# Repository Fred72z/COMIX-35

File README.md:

# COMIX-35 revision 1.2a

Le COMIX-35 est la réplique d'un ordinateur des années 1980, le COMX-35.
Il utilise le processeur COSMAC 1802 et dispose de 32K de mémoire vive et 3K de mémoir vidéo.

Cette version (1.2a) est une légère amélioration du COMIX-35 réalisé par "schlae".  
https://github.com/schlae/comix-35

Les améliorations sont : 
- le pcb est moins large (295mm) pour faciliter l'impression d'un boîtier
- les résistances ajustables sont verticales et plus petites
- le potentiomètre de volume est sur le côté G
- l'inter d'alimentation est vertical
- le connecteur d'extension est un modèle IDC 40 broches
- le circuit K7in est remplacé par un LM358 pour faciliter le chargement sans réglage de seuil.

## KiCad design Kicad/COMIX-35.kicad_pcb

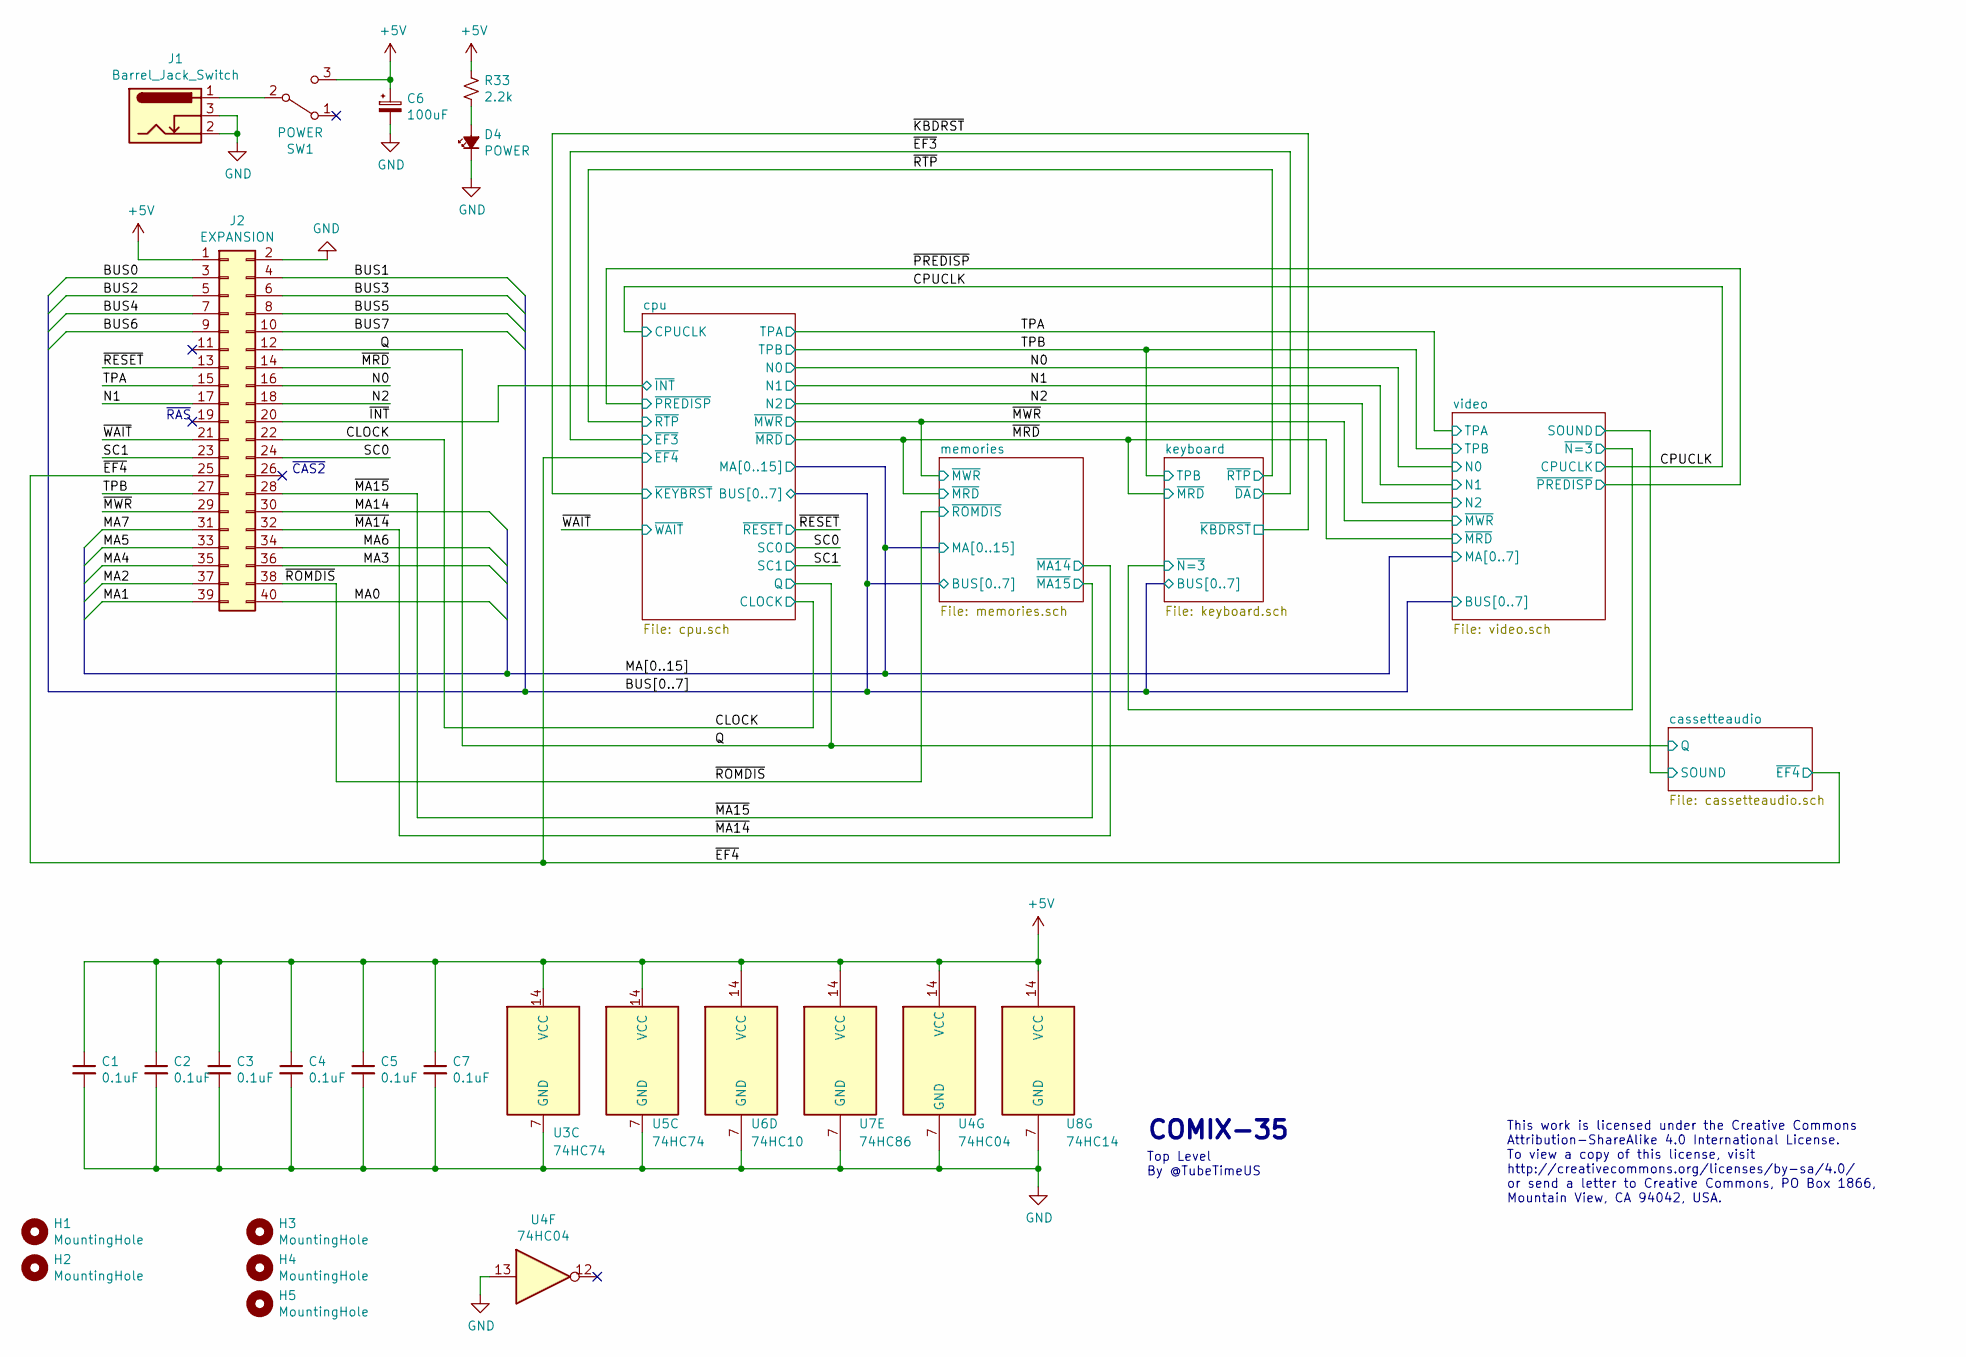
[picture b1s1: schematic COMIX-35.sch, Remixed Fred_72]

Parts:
C1, C2, C3, C4, C5, C7: 0.1uF; CAPAC200; Mouser 581-SA105E104M
C6: 100uF; CAPAE200P500X1100; Mouser 667-ECA-1CM101I
D4: POWER; LED_D5.0mm; Mouser 859-LTL-4213
H1, H2, H3, H4, H5: MountingHole; MountingHole_3.2mm_M3_DIN965
J1: Barrel_Jack_Switch; CUI_PJ-002B; Mouser 490-PJ-002B
J2: EXPANSION; IDC-Header_2x20_P2.54mm_Horizontal
R33: 2.2k; RESA500; Mouser 603-CFR-25JR-52220R
SW1: POWER; T8020L; Mouser 633-CS12ANW03
U3, U5: 74HC74; DIP-14_W7.62mm; Mouser 595-SN74HC74N
U4: 74HC04; DIP-14_W7.62mm; Mouser 595-SN74HCU04N
U6: 74HC10; DIP-14_W7.62mm; Mouser 595-SN74HC10N
U7: 74HC86; DIP-14_W7.62mm; Mouser 595-SN74HC86N
U8: 74HC14; DIP-14_W7.62mm; Mouser 595-SN74HC14N

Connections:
+5V: C1.1, C2.1, C3.1, C4.1, C5.1, C6.1, C7.1, J2.1, R33.2, SW1.3 (C), U3.14 (VCC), U4.14 (VCC), U5.14 (VCC), U6.14 (VCC), U7.14 (VCC), U8.14 (VCC); also elsewhere on the board
/BUS0: J2.3; also elsewhere on the board
/BUS1: J2.4; also elsewhere on the board
/BUS2: J2.5; also elsewhere on the board
/BUS3: J2.6; also elsewhere on the board
/BUS4: J2.7; also elsewhere on the board
/BUS5: J2.8; also elsewhere on the board
/BUS6: J2.9; also elsewhere on the board
/BUS7: J2.10; also elsewhere on the board
/CLOCK: J2.22; also elsewhere on the board
/MA0: J2.40; also elsewhere on the board
/MA1: J2.39; also elsewhere on the board
/MA2: J2.37; also elsewhere on the board
/MA3: J2.36; also elsewhere on the board
/MA4: J2.35; also elsewhere on the board
/MA5: J2.33; also elsewhere on the board
/MA6: J2.34; also elsewhere on the board
/MA7: J2.31; also elsewhere on the board
/MA14: J2.30; also elsewhere on the board
/N0: J2.16; also elsewhere on the board
/N1: J2.17; also elsewhere on the board
/N2: J2.18; also elsewhere on the board
/Q: J2.12; also elsewhere on the board
/SC0: J2.24; also elsewhere on the board
/SC1: J2.23; also elsewhere on the board
/TPA: J2.15; also elsewhere on the board
/TPB: J2.27; also elsewhere on the board
/~EF4: J2.25; also elsewhere on the board
/~INT: J2.20; also elsewhere on the board
/~MA14: J2.32; also elsewhere on the board
/~MA15: J2.28; also elsewhere on the board
/~MRD: J2.14; also elsewhere on the board
/~MWR: J2.29; also elsewhere on the board
/~RESET: J2.13; also elsewhere on the board
/~ROMDIS: J2.38; also elsewhere on the board
/~WAIT: J2.21; also elsewhere on the board
GND: C1.2, C2.2, C3.2, C4.2, C5.2, C6.2, C7.2, D4.1 (K), J1.2, J1.3, J2.2, U3.7 (GND), U4.7 (GND), U4.13, U5.7 (GND), U6.7 (GND), U7.7 (GND), U8.7 (GND); also elsewhere on the board
unnamed: D4.2 (A), R33.1
unnamed: J1.1, SW1.2 (B)

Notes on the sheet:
~RAS
~CAS2
This work is licensed under the Creative Commons Attribution-ShareAlike 4.0 International License. To view a copy of this license, visit http://creativecommons.org/licenses/by-sa/4.0/ or send a letter to Creative Commons, PO Box 1866, Mountain View, CA 94042, USA.
COMIX-35
Top Level By @TubeTimeUS

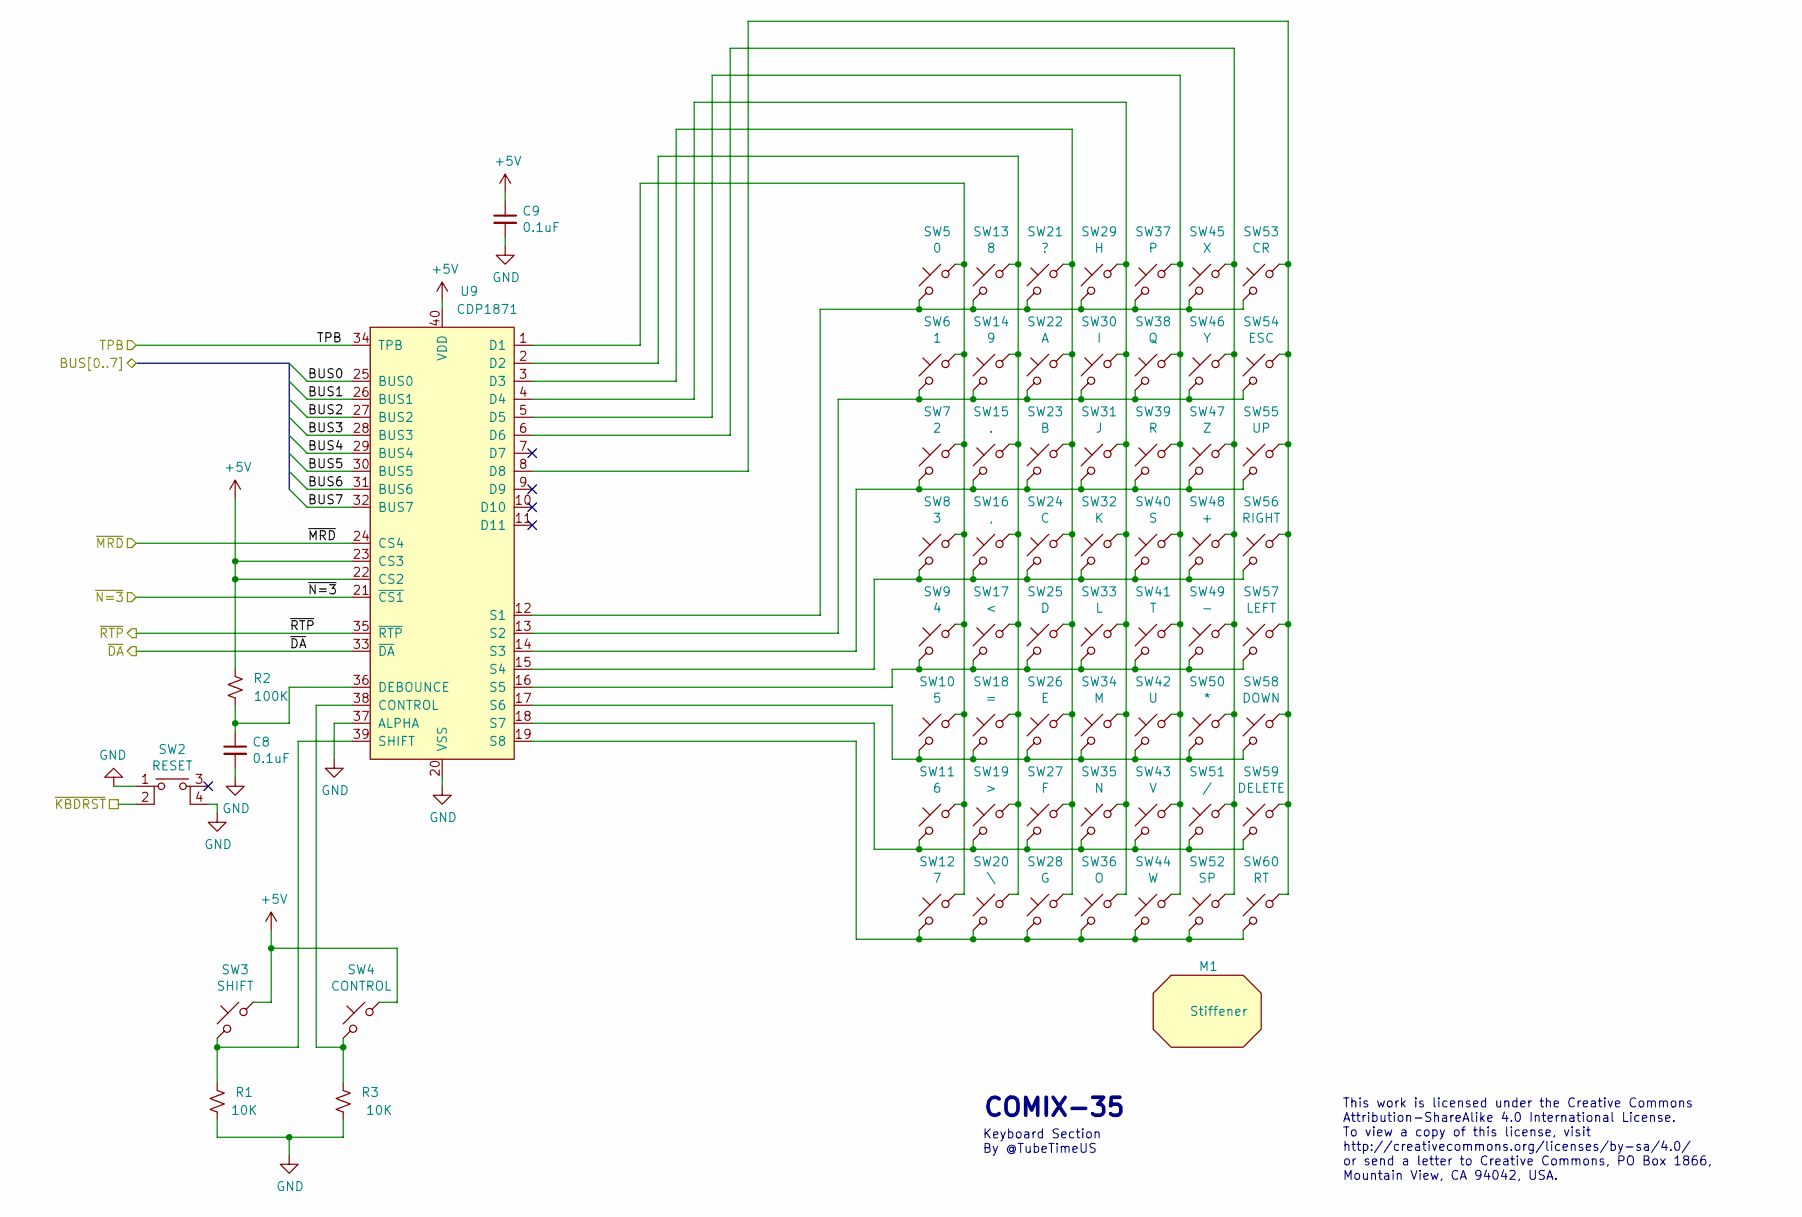
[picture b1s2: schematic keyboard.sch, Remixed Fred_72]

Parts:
C8, C9: 0.1uF; CAPAC200; Mouser 581-SA105E104M
M1: Stiffener; CHERRY_ST2; Mouser 540-0G990743
R1, R3: 10K; RESA500; Mouser 603-CFR-25JB-52-10K
R2: 100K; RESA500; Mouser 603-CFR-25JB-52-100K
SW2: RESET; SW_Tactile_SPST_Angled_PTS645Vx58-2LFS; Mouser 612-TL1105B
SW3: SHIFT; CHERRY_MX_125; Mouser 540-MX1A-11NW
SW4: CONTROL; CHERRY_MX; Mouser 540-MX1A-11NW
SW5: 0; CHERRY_MX; Mouser 540-MX1A-11NW
SW6: 1; CHERRY_MX; Mouser 540-MX1A-11NW
SW7: 2; CHERRY_MX; Mouser 540-MX1A-11NW
SW8: 3; CHERRY_MX; Mouser 540-MX1A-11NW
SW9: 4; CHERRY_MX; Mouser 540-MX1A-11NW
SW10: 5; CHERRY_MX; Mouser 540-MX1A-11NW
SW11: 6; CHERRY_MX; Mouser 540-MX1A-11NW
SW12: 7; CHERRY_MX; Mouser 540-MX1A-11NW
SW13: 8; CHERRY_MX; Mouser 540-MX1A-11NW
SW14: 9; CHERRY_MX; Mouser 540-MX1A-11NW
SW15: .; CHERRY_MX; Mouser 540-MX1A-11NW
SW16: ,; CHERRY_MX; Mouser 540-MX1A-11NW
SW17: <; CHERRY_MX; Mouser 540-MX1A-11NW
SW18: =; CHERRY_MX; Mouser 540-MX1A-11NW
SW19: >; CHERRY_MX; Mouser 540-MX1A-11NW
SW20: \\; CHERRY_MX; Mouser 540-MX1A-11NW
SW21: ?; CHERRY_MX; Mouser 540-MX1A-11NW
SW22: A; CHERRY_MX; Mouser 540-MX1A-11NW
SW23: B; CHERRY_MX; Mouser 540-MX1A-11NW
SW24: C; CHERRY_MX; Mouser 540-MX1A-11NW
SW25: D; CHERRY_MX; Mouser 540-MX1A-11NW
SW26: E; CHERRY_MX; Mouser 540-MX1A-11NW
SW27: F; CHERRY_MX; Mouser 540-MX1A-11NW
SW28: G; CHERRY_MX; Mouser 540-MX1A-11NW
SW29: H; CHERRY_MX; Mouser 540-MX1A-11NW
SW30: I; CHERRY_MX; Mouser 540-MX1A-11NW
SW31: J; CHERRY_MX; Mouser 540-MX1A-11NW
SW32: K; CHERRY_MX; Mouser 540-MX1A-11NW
SW33: L; CHERRY_MX; Mouser 540-MX1A-11NW
SW34: M; CHERRY_MX; Mouser 540-MX1A-11NW
SW35: N; CHERRY_MX; Mouser 540-MX1A-11NW
SW36: O; CHERRY_MX; Mouser 540-MX1A-11NW
SW37: P; CHERRY_MX; Mouser 540-MX1A-11NW
SW38: Q; CHERRY_MX; Mouser 540-MX1A-11NW
SW39: R; CHERRY_MX; Mouser 540-MX1A-11NW
SW40: S; CHERRY_MX; Mouser 540-MX1A-11NW
SW41: T; CHERRY_MX; Mouser 540-MX1A-11NW
SW42: U; CHERRY_MX; Mouser 540-MX1A-11NW
SW43: V; CHERRY_MX; Mouser 540-MX1A-11NW
SW44: W; CHERRY_MX; Mouser 540-MX1A-11NW
SW45: X; CHERRY_MX; Mouser 540-MX1A-11NW
SW46: Y; CHERRY_MX; Mouser 540-MX1A-11NW
SW47: Z; CHERRY_MX; Mouser 540-MX1A-11NW
SW48: +; CHERRY_MX; Mouser 540-MX1A-11NW
SW49: -; CHERRY_MX; Mouser 540-MX1A-11NW
SW50: *; CHERRY_MX; Mouser 540-MX1A-11NW
SW51: /; CHERRY_MX; Mouser 540-MX1A-11NW
SW52: SP; CHERRY_MX_625; Mouser 540-MX1A-11NW
SW53: CR; CHERRY_MX_150; Mouser 540-MX1A-11NW
SW54: ESC; CHERRY_MX; Mouser 540-MX1A-11NW
SW55: UP; CHERRY_MX; Mouser 540-MX1A-11NW
SW56: RIGHT; CHERRY_MX; Mouser 540-MX1A-11NW
SW57: LEFT; CHERRY_MX; Mouser 540-MX1A-11NW
SW58: DOWN; CHERRY_MX; Mouser 540-MX1A-11NW
SW59: DELETE; CHERRY_MX; Mouser 540-MX1A-11NW
SW60: RT; CHERRY_MX; Mouser 540-MX1A-11NW
U9: CDP1871; DIP-40_W15.24mm

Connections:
+5V: C9.1, R2.1, SW3.1, SW4.1, U9.22 (CS2), U9.23 (CS3), U9.40 (VDD); also elsewhere on the board
/BUS0: U9.25 (BUS0); also elsewhere on the board
/BUS1: U9.26 (BUS1); also elsewhere on the board
/BUS2: U9.27 (BUS2); also elsewhere on the board
/BUS3: U9.28 (BUS3); also elsewhere on the board
/BUS4: U9.29 (BUS4); also elsewhere on the board
/BUS5: U9.30 (BUS5); also elsewhere on the board
/BUS6: U9.31 (BUS6); also elsewhere on the board
/BUS7: U9.32 (BUS7); also elsewhere on the board
/TPB: U9.34 (TPB); also elsewhere on the board
/keyboard/~N=3: U9.21 (~CS1); also elsewhere on the board
/~EF3: U9.33 (~DA); also elsewhere on the board
/~KBDRST: SW2.2; also elsewhere on the board
/~MRD: U9.24 (CS4); also elsewhere on the board
/~RTP: U9.35 (~RTP); also elsewhere on the board
GND: C8.2, C9.2, R1.2, R3.2, SW2.1, SW2.4, U9.20 (VSS), U9.37 (ALPHA); also elsewhere on the board
unnamed: C8.1, R2.2, U9.36 (DEBOUNCE)
unnamed: R1.1, SW3.2, U9.39 (SHIFT)
unnamed: R3.1, SW4.2, U9.38 (CONTROL)
unnamed: SW5.1, SW6.1, SW7.1, SW8.1, SW9.1, SW10.1, SW11.1, SW12.1, U9.1 (D1)
unnamed: SW10.2, SW18.2, SW26.2, SW34.2, SW42.2, SW50.2, SW58.2, U9.17 (S6)
unnamed: SW11.2, SW19.2, SW27.2, SW35.2, SW43.2, SW51.2, SW59.2, U9.18 (S7)
unnamed: SW12.2, SW20.2, SW28.2, SW36.2, SW44.2, SW52.2, SW60.2, U9.19 (S8)
unnamed: SW13.1, SW14.1, SW15.1, SW16.1, SW17.1, SW18.1, SW19.1, SW20.1, U9.2 (D2)
unnamed: SW5.2, SW13.2, SW21.2, SW29.2, SW37.2, SW45.2, SW53.2, U9.12 (S1)
unnamed: SW6.2, SW14.2, SW22.2, SW30.2, SW38.2, SW46.2, SW54.2, U9.13 (S2)
unnamed: SW7.2, SW15.2, SW23.2, SW31.2, SW39.2, SW47.2, SW55.2, U9.14 (S3)
unnamed: SW8.2, SW16.2, SW24.2, SW32.2, SW40.2, SW48.2, SW56.2, U9.15 (S4)
unnamed: SW9.2, SW17.2, SW25.2, SW33.2, SW41.2, SW49.2, SW57.2, U9.16 (S5)
unnamed: SW21.1, SW22.1, SW23.1, SW24.1, SW25.1, SW26.1, SW27.1, SW28.1, U9.3 (D3)
unnamed: SW29.1, SW30.1, SW31.1, SW32.1, SW33.1, SW34.1, SW35.1, SW36.1, U9.4 (D4)
unnamed: SW37.1, SW38.1, SW39.1, SW40.1, SW41.1, SW42.1, SW43.1, SW44.1, U9.5 (D5)
unnamed: SW45.1, SW46.1, SW47.1, SW48.1, SW49.1, SW50.1, SW51.1, SW52.1, U9.6 (D6)
unnamed: SW53.1, SW54.1, SW55.1, SW56.1, SW57.1, SW58.1, SW59.1, SW60.1, U9.8 (D8)

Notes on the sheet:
This work is licensed under the Creative Commons Attribution-ShareAlike 4.0 International License. To view a copy of this license, visit http://creativecommons.org/licenses/by-sa/4.0/ or send a letter to Creative Commons, PO Box 1866, Mountain View, CA 94042, USA.
COMIX-35
Keyboard Section By @TubeTimeUS

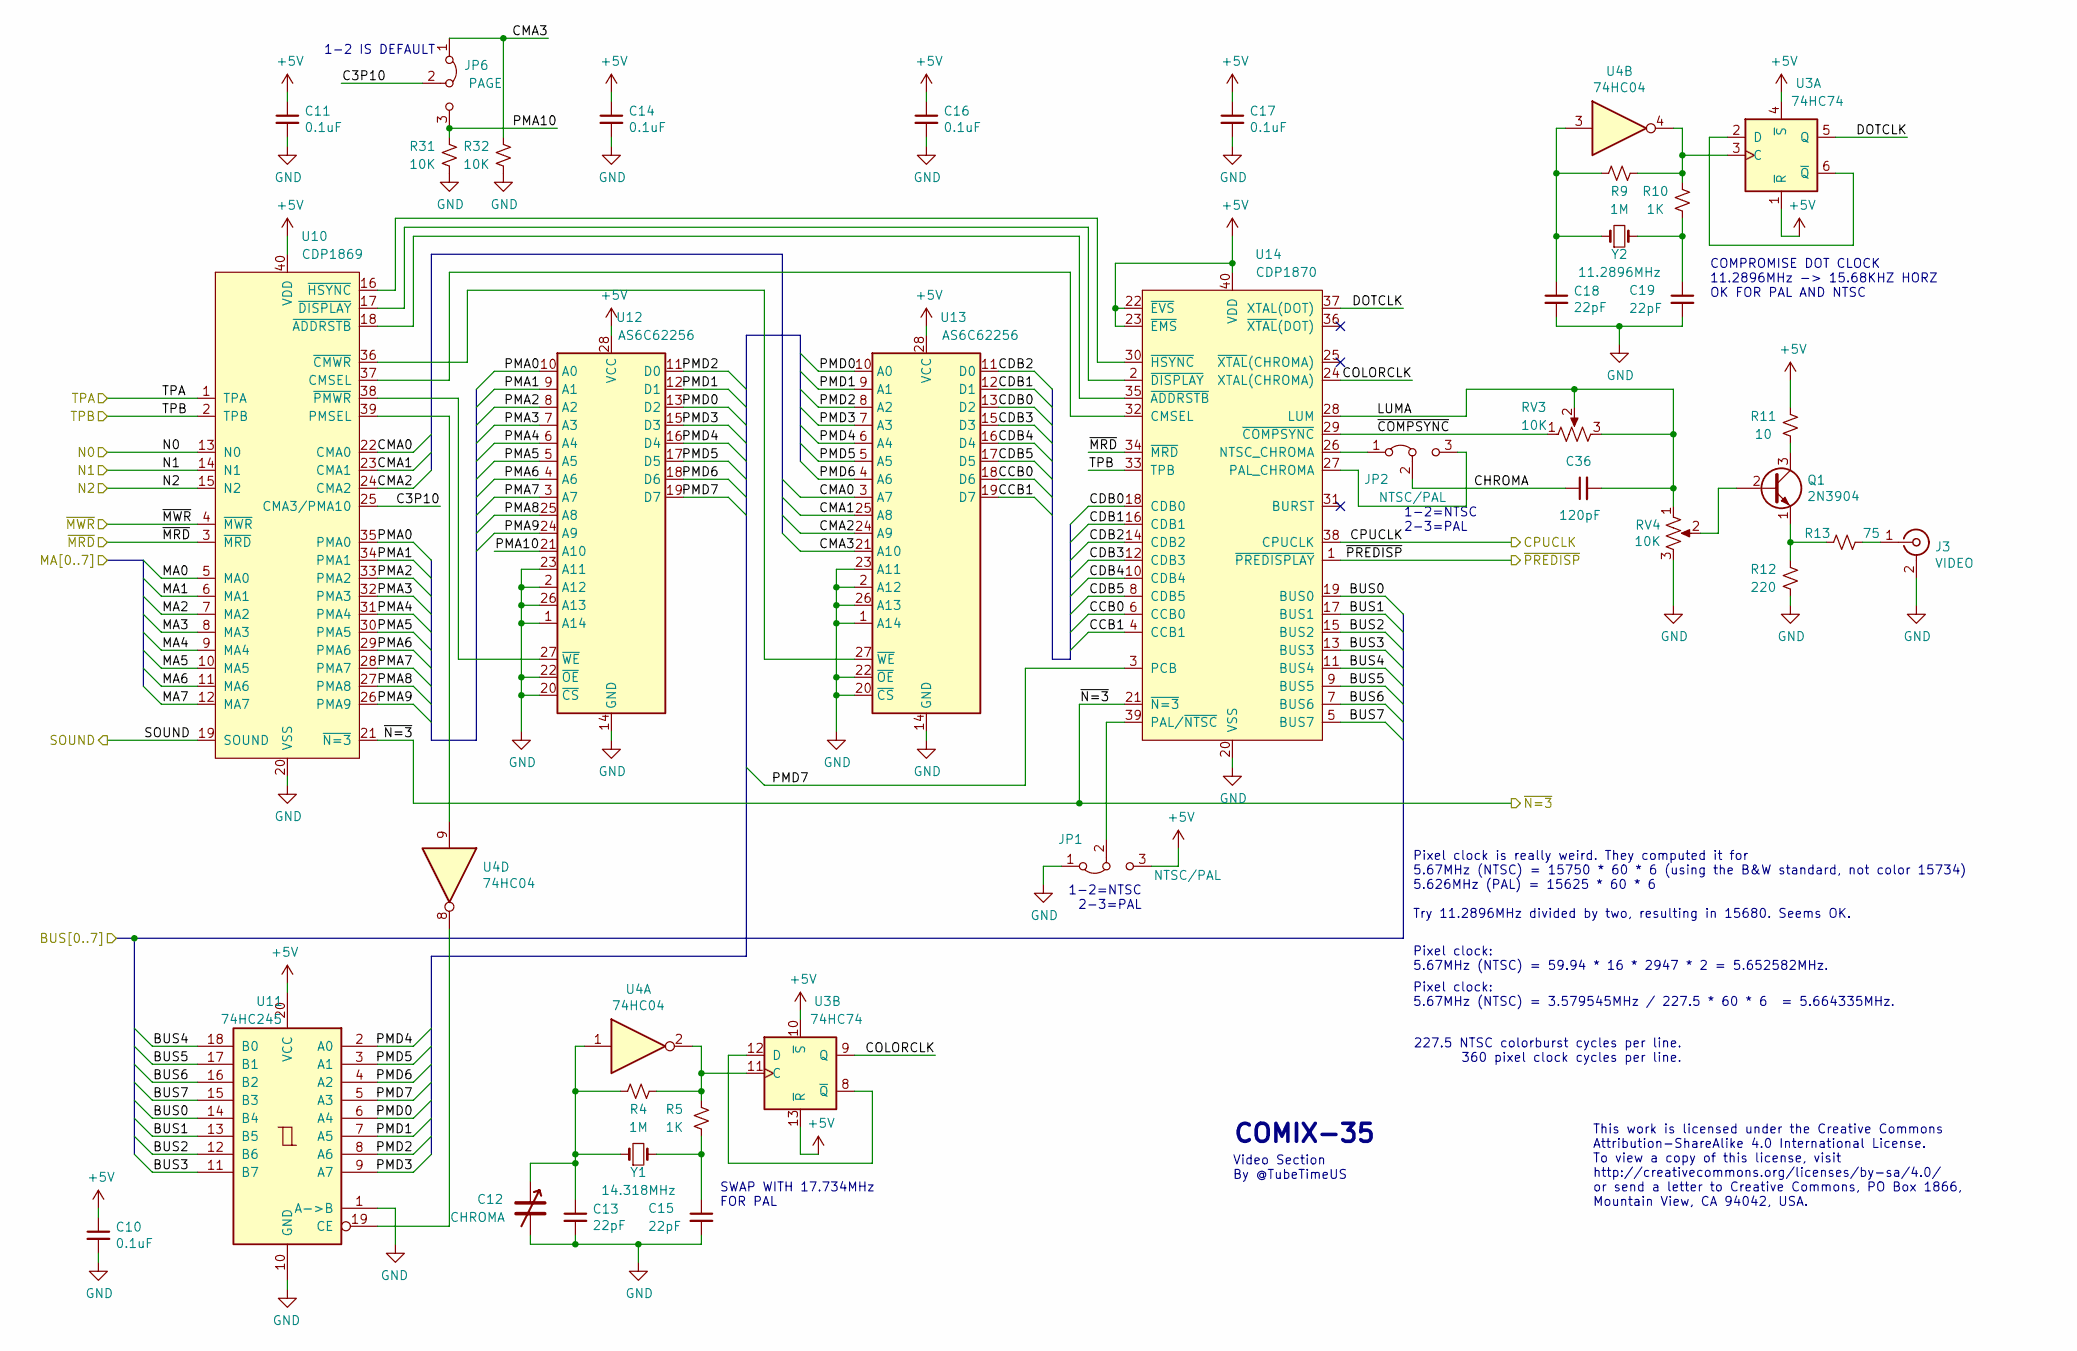
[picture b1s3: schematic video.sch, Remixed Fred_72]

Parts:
C10, C11, C14, C16, C17: 0.1uF; CAPAC200; Mouser 581-SA105E104M
C12: CHROMA; EW_GKG; Digikey 2447-GKG30015-ND
C13, C15, C18, C19: 22pF; CAPAC200; Mouser 810-FG28C0G2A220JNT0
C36: 120pF; CAPAC200; Mouser 810-FG28C0G1H121JNT6
J3: VIDEO; RCA_metal_Horizontal_L5mm; Mouser 161-0360-E
JP1, JP2: NTSC/PAL; Pin_Header_Straight_1x03_Pitch2.54mm
JP6: PAGE; Pin_Header_Straight_1x03_Pitch2.54mm
Q1: 2N3904; TO92-IL; Mouser 512-2N3904BU
R4, R9: 1M; RESA500; Mouser 603-CFR-25JR-521M
R5, R10: 1K; RESA500; Mouser 603-CFR-25JR-521K
R11: 10; RESA500; Mouser 603-CFR-25JR-5210R
R12: 220; RESA500; Mouser 603-CFR-25JR-52220R
R13: 75; RESA500; Mouser 603-CFR-25JR-5275R
R31, R32: 10K; RESA500; Mouser 603-CFR-25JB-52-10K
RV3, RV4: 10K; Potentiometer_Bourns_3339P_Vertical_HandSoldering; Mouser 531-PT10H-10K-S
U3: 74HC74; DIP-14_W7.62mm; Mouser 595-SN74HC74N
U4: 74HC04; DIP-14_W7.62mm; Mouser 595-SN74HC04N
U10: CDP1869; DIP-40_W15.24mm
U11: 74HC245; DIP-20_W7.62mm; Mouser 595-SN74HC245N
U12, U13: AS6C62256; DIP-28_W15.24mm; Mouser 913-AS6C62256-55PCN
U14: CDP1870; DIP-40_W15.24mm
Y1: 14.318MHz; Crystal_HC49-4H_Vertical; Mouser 815-ABL-14.31818B2
Y2: 11.2896MHz; Crystal_HC49-4H_Vertical; Mouser 815-ABL-11.2896-B4Y

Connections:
+5V: C10.1, C11.1, C14.1, C16.1, C17.1, JP1.3 (B), R11.1, U3.1 (~R), U3.4 (~S), U3.10 (~S), U3.13 (~R), U10.40 (VDD), U11.20 (VCC), U12.28 (VCC), U13.28 (VCC), U14.22 (~EVS), U14.23 (~EMS), U14.40 (VDD); also elsewhere on the board
/BUS0: U11.14 (B4), U14.19 (BUS0); also elsewhere on the board
/BUS1: U11.13 (B5), U14.17 (BUS1); also elsewhere on the board
/BUS2: U11.12 (B6), U14.15 (BUS2); also elsewhere on the board
/BUS3: U11.11 (B7), U14.13 (BUS3); also elsewhere on the board
/BUS4: U11.18 (B0), U14.11 (BUS4); also elsewhere on the board
/BUS5: U11.17 (B1), U14.9 (BUS5); also elsewhere on the board
/BUS6: U11.16 (B2), U14.7 (BUS6); also elsewhere on the board
/BUS7: U11.15 (B3), U14.5 (BUS7); also elsewhere on the board
/CPUCLK: U14.38 (CPUCLK); also elsewhere on the board
/MA0: U10.5 (MA0); also elsewhere on the board
/MA1: U10.6 (MA1); also elsewhere on the board
/MA2: U10.7 (MA2); also elsewhere on the board
/MA3: U10.8 (MA3); also elsewhere on the board
/MA4: U10.9 (MA4); also elsewhere on the board
/MA5: U10.10 (MA5); also elsewhere on the board
/MA6: U10.11 (MA6); also elsewhere on the board
/MA7: U10.12 (MA7); also elsewhere on the board
/N0: U10.13 (N0); also elsewhere on the board
/N1: U10.14 (N1); also elsewhere on the board
/N2: U10.15 (N2); also elsewhere on the board
/TPA: U10.1 (TPA); also elsewhere on the board
/TPB: U10.2 (TPB), U14.33 (TPB); also elsewhere on the board
/cassetteaudio/SOUND: U10.19 (SOUND); also elsewhere on the board
/keyboard/~N=3: U10.21 (~N=3), U14.21 (~N=3); also elsewhere on the board
/video/C3P10: JP6.2 (C), U10.25 (CMA3/PMA10)
/video/CCB0: U13.18 (D6), U14.6 (CCB0)
/video/CCB1: U13.19 (D7), U14.4 (CCB1)
/video/CDB0: U13.13 (D2), U14.18 (CDB0)
/video/CDB1: U13.12 (D1), U14.16 (CDB1)
/video/CDB2: U13.11 (D0), U14.14 (CDB2)
/video/CDB3: U13.15 (D3), U14.12 (CDB3)
/video/CDB4: U13.16 (D4), U14.10 (CDB4)
/video/CDB5: U13.17 (D5), U14.8 (CDB5)
/video/CHROMA: C36.1, JP2.2 (C)
/video/CMA0: U10.22 (CMA0), U13.3 (A7)
/video/CMA1: U10.23 (CMA1), U13.25 (A8)
/video/CMA2: U10.24 (CMA2), U13.24 (A9)
/video/CMA3: JP6.1 (A), R32.1, U13.21 (A10)
/video/COLORCLK: U3.9 (Q), U14.24 (XTAL(CHROMA))
/video/DOTCLK: U3.5 (Q), U14.37 (XTAL(DOT))
/video/LUMA: C36.2, RV3.2, RV3.3, RV4.1, U14.28 (LUM)
/video/PMA0: U10.35 (PMA0), U12.10 (A0)
/video/PMA1: U10.34 (PMA1), U12.9 (A1)
/video/PMA2: U10.33 (PMA2), U12.8 (A2)
/video/PMA3: U10.32 (PMA3), U12.7 (A3)
/video/PMA4: U10.31 (PMA4), U12.6 (A4)
/video/PMA5: U10.30 (PMA5), U12.5 (A5)
/video/PMA6: U10.29 (PMA6), U12.4 (A6)
/video/PMA7: U10.28 (PMA7), U12.3 (A7)
/video/PMA8: U10.27 (PMA8), U12.25 (A8)
/video/PMA9: U10.26 (PMA9), U12.24 (A9)
/video/PMA10: JP6.3 (B), R31.1, U12.21 (A10)
/video/PMD0: U11.6 (A4), U12.13 (D2), U13.10 (A0)
/video/PMD1: U11.7 (A5), U12.12 (D1), U13.9 (A1)
/video/PMD2: U11.8 (A6), U12.11 (D0), U13.8 (A2)
/video/PMD3: U11.9 (A7), U12.15 (D3), U13.7 (A3)
/video/PMD4: U11.2 (A0), U12.16 (D4), U13.6 (A4)
/video/PMD5: U11.3 (A1), U12.17 (D5), U13.5 (A5)
/video/PMD6: U11.4 (A2), U12.18 (D6), U13.4 (A6)
/video/PMD7: U11.5 (A3), U12.19 (D7), U14.3 (PCB)
/video/~COMPSYNC: RV3.1, U14.29 (~COMPSYNC)
/~MRD: U10.3 (~MRD), U14.34 (~MRD); also elsewhere on the board
/~MWR: U10.4 (~MWR); also elsewhere on the board
/~PREDISP: U14.1 (~PREDISPLAY); also elsewhere on the board
GND: C10.2, C11.2, C12.2, C13.2, C14.2, C15.2, C16.2, C17.2, C18.2, C19.2, J3.2 (Ext), JP1.1 (A), R12.2, R31.2, R32.2, RV4.3, U10.20 (VSS), U11.1 (A->B), U11.10 (GND), U12.1 (A14), U12.2 (A12), U12.14 (GND), U12.20 (~CS), U12.22 (~OE), U12.23 (A11), U12.26 (A13), U13.1 (A14), U13.2 (A12), U13.14 (GND), U13.20 (~CS), U13.22 (~OE), U13.23 (A11), U13.26 (A13), U14.20 (VSS); also elsewhere on the board
unnamed: C12.1, C13.1, R4.1, U4.1, Y1.1
unnamed: C15.1, R5.2, Y1.2
unnamed: C18.1, R9.1, U4.3, Y2.1
unnamed: C19.1, R10.2, Y2.2
unnamed: J3.1 (In), R13.2
unnamed: JP1.2 (C), U14.39 (PAL/~NTSC)
unnamed: JP2.1 (A), U14.26 (NTSC_CHROMA)
unnamed: JP2.3 (B), U14.27 (PAL_CHROMA)
unnamed: Q1.1 (E), R12.1, R13.1
unnamed: Q1.2 (B), RV4.2
unnamed: Q1.3 (C), R11.2
unnamed: R4.2, R5.1, U3.11 (C), U4.2
unnamed: R9.2, R10.1, U3.3 (C), U4.4
unnamed: U3.2 (D), U3.6 (~Q)
unnamed: U3.8 (~Q), U3.12 (D)
unnamed: U10.16 (~HSYNC), U14.30 (~HSYNC)
unnamed: U10.17 (~DISPLAY), U14.2 (~DISPLAY)
unnamed: U10.18 (~ADDRSTB), U14.35 (~ADDRSTB)
unnamed: U10.36 (~CMWR), U13.27 (~WE)
unnamed: U10.37 (CMSEL), U14.32 (CMSEL)
unnamed: U10.38 (~PMWR), U12.27 (~WE)
unnamed: U4.9, U10.39 (PMSEL)
unnamed: U4.8, U11.19 (CE)

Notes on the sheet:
COMPROMISE DOT CLOCK 11.2896MHz -> 15.68KHZ HORZ OK FOR PAL AND NTSC
SWAP WITH 17.734MHz FOR PAL
1-2=NTSC 2-3=PAL
Pixel clock is really weird. They computed it for 5.67MHz (NTSC) = 15750 * 60 * 6 (using the B&W standard, not color 15734) 5.626MHz (PAL) = 15625 * 60 * 6 Try 11.2896MHz divided by two, resulting in 15680. Seems OK.
Pixel clock: 5.67MHz (NTSC) = 59.94 * 16 * 2947 * 2 = 5.652582MHz.
Pixel clock: 5.67MHz (NTSC) = 3.579545MHz / 227.5 * 60 * 6 = 5.664335MHz.
227.5 NTSC colorburst cycles per line. 360 pixel clock cycles per line.
1-2 IS DEFAULT
This work is licensed under the Creative Commons Attribution-ShareAlike 4.0 International License. To view a copy of this license, visit http://creativecommons.org/licenses/by-sa/4.0/ or send a letter to Creative Commons, PO Box 1866, Mountain View, CA 94042, USA.
COMIX-35
Video Section By @TubeTimeUS

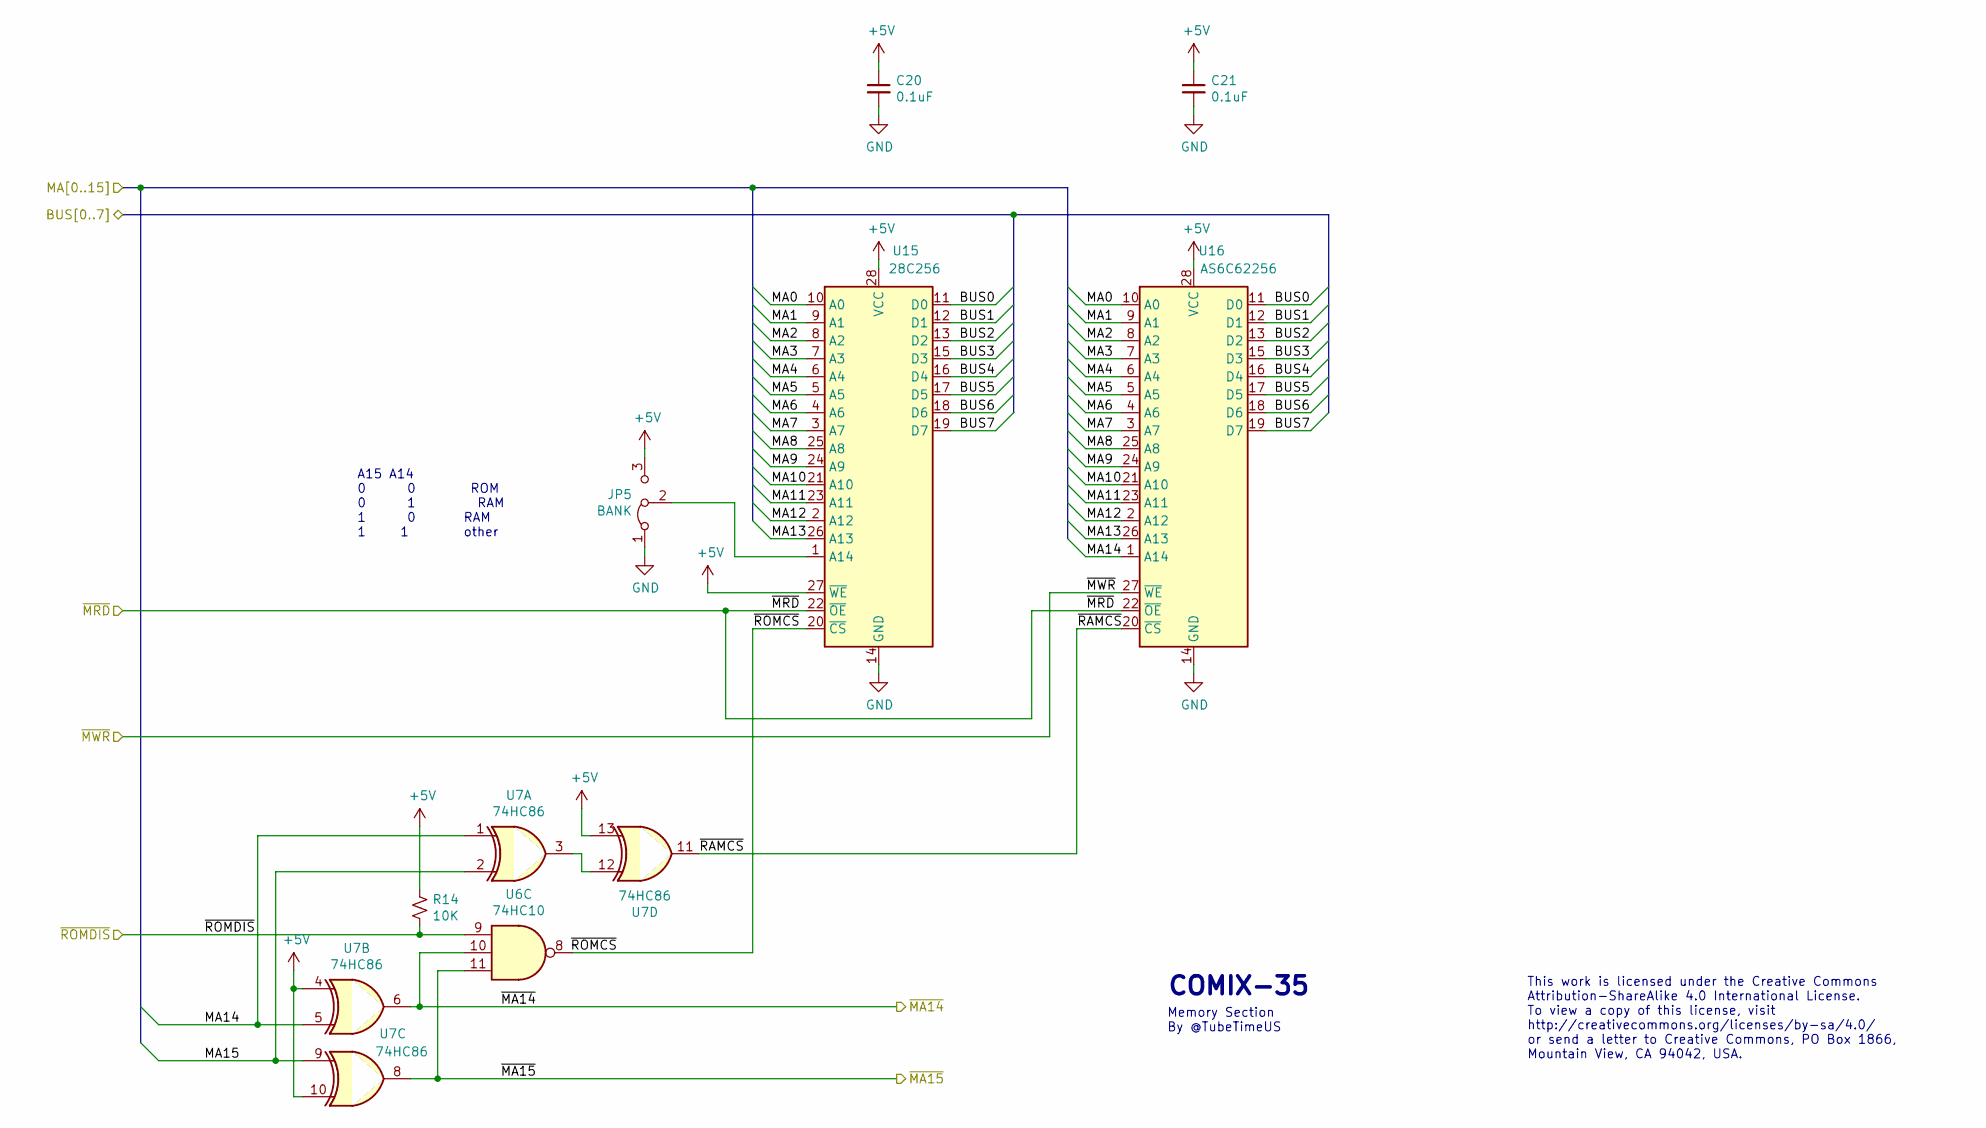
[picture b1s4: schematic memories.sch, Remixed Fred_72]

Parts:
C20, C21: 0.1uF; CAPAC200; Mouser 581-SA105E104M
JP5: BANK; Pin_Header_Straight_1x03_Pitch2.54mm
R14: 10K; RESA500; Mouser 603-CFR-25JB-52-10K
U6: 74HC10; DIP-14_W7.62mm; Mouser 595-SN74HC10N
U7: 74HC86; DIP-14_W7.62mm; Mouser 595-SN74HC86N
U15: 28C256; DIP-28_W15.24mm; Mouser 556-AT28C25615PU
U16: AS6C62256; DIP-28_W15.24mm; Mouser 913-AS6C62256-55PCN

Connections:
+5V: C20.1, C21.1, JP5.3 (B), R14.2, U7.4, U7.10, U7.13, U15.27 (~WE), U15.28 (VCC), U16.28 (VCC); also elsewhere on the board
/BUS0: U15.11 (D0), U16.11 (D0); also elsewhere on the board
/BUS1: U15.12 (D1), U16.12 (D1); also elsewhere on the board
/BUS2: U15.13 (D2), U16.13 (D2); also elsewhere on the board
/BUS3: U15.15 (D3), U16.15 (D3); also elsewhere on the board
/BUS4: U15.16 (D4), U16.16 (D4); also elsewhere on the board
/BUS5: U15.17 (D5), U16.17 (D5); also elsewhere on the board
/BUS6: U15.18 (D6), U16.18 (D6); also elsewhere on the board
/BUS7: U15.19 (D7), U16.19 (D7); also elsewhere on the board
/MA0: U15.10 (A0), U16.10 (A0); also elsewhere on the board
/MA1: U15.9 (A1), U16.9 (A1); also elsewhere on the board
/MA2: U15.8 (A2), U16.8 (A2); also elsewhere on the board
/MA3: U15.7 (A3), U16.7 (A3); also elsewhere on the board
/MA4: U15.6 (A4), U16.6 (A4); also elsewhere on the board
/MA5: U15.5 (A5), U16.5 (A5); also elsewhere on the board
/MA6: U15.4 (A6), U16.4 (A6); also elsewhere on the board
/MA7: U15.3 (A7), U16.3 (A7); also elsewhere on the board
/MA14: U7.1, U7.5, U16.1 (A14); also elsewhere on the board
/cpu/MA8: U15.25 (A8), U16.25 (A8); also elsewhere on the board
/cpu/MA9: U15.24 (A9), U16.24 (A9); also elsewhere on the board
/cpu/MA10: U15.21 (A10), U16.21 (A10); also elsewhere on the board
/cpu/MA11: U15.23 (A11), U16.23 (A11); also elsewhere on the board
/cpu/MA12: U15.2 (A12), U16.2 (A12); also elsewhere on the board
/cpu/MA13: U15.26 (A13), U16.26 (A13); also elsewhere on the board
/cpu/MA15: U7.2, U7.9; also elsewhere on the board
/memories/~RAMCS: U7.11, U16.20 (~CS)
/memories/~ROMCS: U6.8, U15.20 (~CS)
/~MA14: U6.10, U7.6; also elsewhere on the board
/~MA15: U6.11, U7.8; also elsewhere on the board
/~MRD: U15.22 (~OE), U16.22 (~OE); also elsewhere on the board
/~MWR: U16.27 (~WE); also elsewhere on the board
/~ROMDIS: R14.1, U6.9; also elsewhere on the board
GND: C20.2, C21.2, JP5.1 (A), U15.14 (GND), U16.14 (GND); also elsewhere on the board
unnamed: JP5.2 (C), U15.1 (A14)
unnamed: U7.3, U7.12

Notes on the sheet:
A15 A14 0 0 ROM 0 1 RAM 1 0 RAM 1 1 other
This work is licensed under the Creative Commons Attribution-ShareAlike 4.0 International License. To view a copy of this license, visit http://creativecommons.org/licenses/by-sa/4.0/ or send a letter to Creative Commons, PO Box 1866, Mountain View, CA 94042, USA.
COMIX-35
Memory Section By @TubeTimeUS

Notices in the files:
Kicad/COMIX-35.kicad_pcb:
Copyright (C) 2020 Eric Schlaepfer
License. See https://creativecommons.org/licenses/by-sa/4.0
This work is licensed under a Creative Commons Attribution-ShareAlike 4.0 International
©2020 Tube Time
